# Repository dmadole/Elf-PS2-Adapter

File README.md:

# Elf-PS2-Adapter

This is a very simple adapter to use a PS/2 type keyboard on a typical 1802 "Elf" computer system. It uses the Q output and an EF input (typically EF2) to interface to the keyboard. It works by using Q to both control the clock line output and to multiplex the EF line between the clock and data line for input.

This can be used with the 9918 Video and PS/2 keyboard driver for Elf/OS:
https://github.com/dmadole/Elfos-pstwo

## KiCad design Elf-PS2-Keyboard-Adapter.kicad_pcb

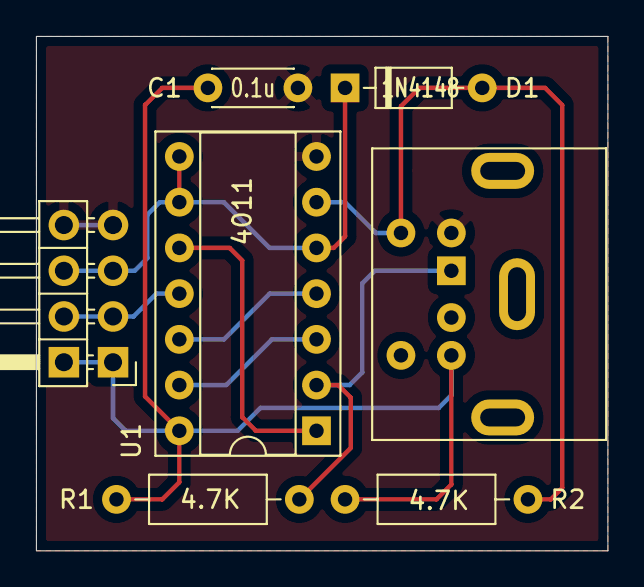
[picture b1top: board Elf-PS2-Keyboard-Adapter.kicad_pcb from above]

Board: 2 copper layers, 31.8 x 28.6 mm, 8 parts (1 on the bottom side), 9 nets.

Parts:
C1: C; C_Disc_D4.3mm_W1.9mm_P5.00mm
D1: 1N4148; D_DO-35_SOD27_P7.62mm_Horizontal
J1: Mini-DIN-6; 6-pin-mini-din
J2: Conn_01x04; PinHeader_1x04_P2.54mm_Horizontal
J3: Conn_01x04; PinHeader_1x04_P2.54mm_Vertical
R1, R2: 4.7K; R_Axial_DIN0207_L6.3mm_D2.5mm_P10.16mm_Horizontal
U1: 4011; DIP-14_W7.62mm_Socket

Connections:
GND: C1.2, J1.3, J2.4, J3.4, U1.7
unnamed: D1.1, J2.3, J3.3, U1.5, U1.8, U1.9
unnamed: D1.2, J1.5, R2.2, U1.6
unnamed: J1.1, R1.2, U1.2
unnamed: J2.2, J3.2, U1.11
unnamed: U1.1, U1.10
unnamed: U1.4, U1.12
unnamed: U1.3, U1.13
VCC: C1.1, J1.4, J2.1, J3.1, R1.1, R2.1, U1.14

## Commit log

2022-03-13 Update README.md
    Add photo
